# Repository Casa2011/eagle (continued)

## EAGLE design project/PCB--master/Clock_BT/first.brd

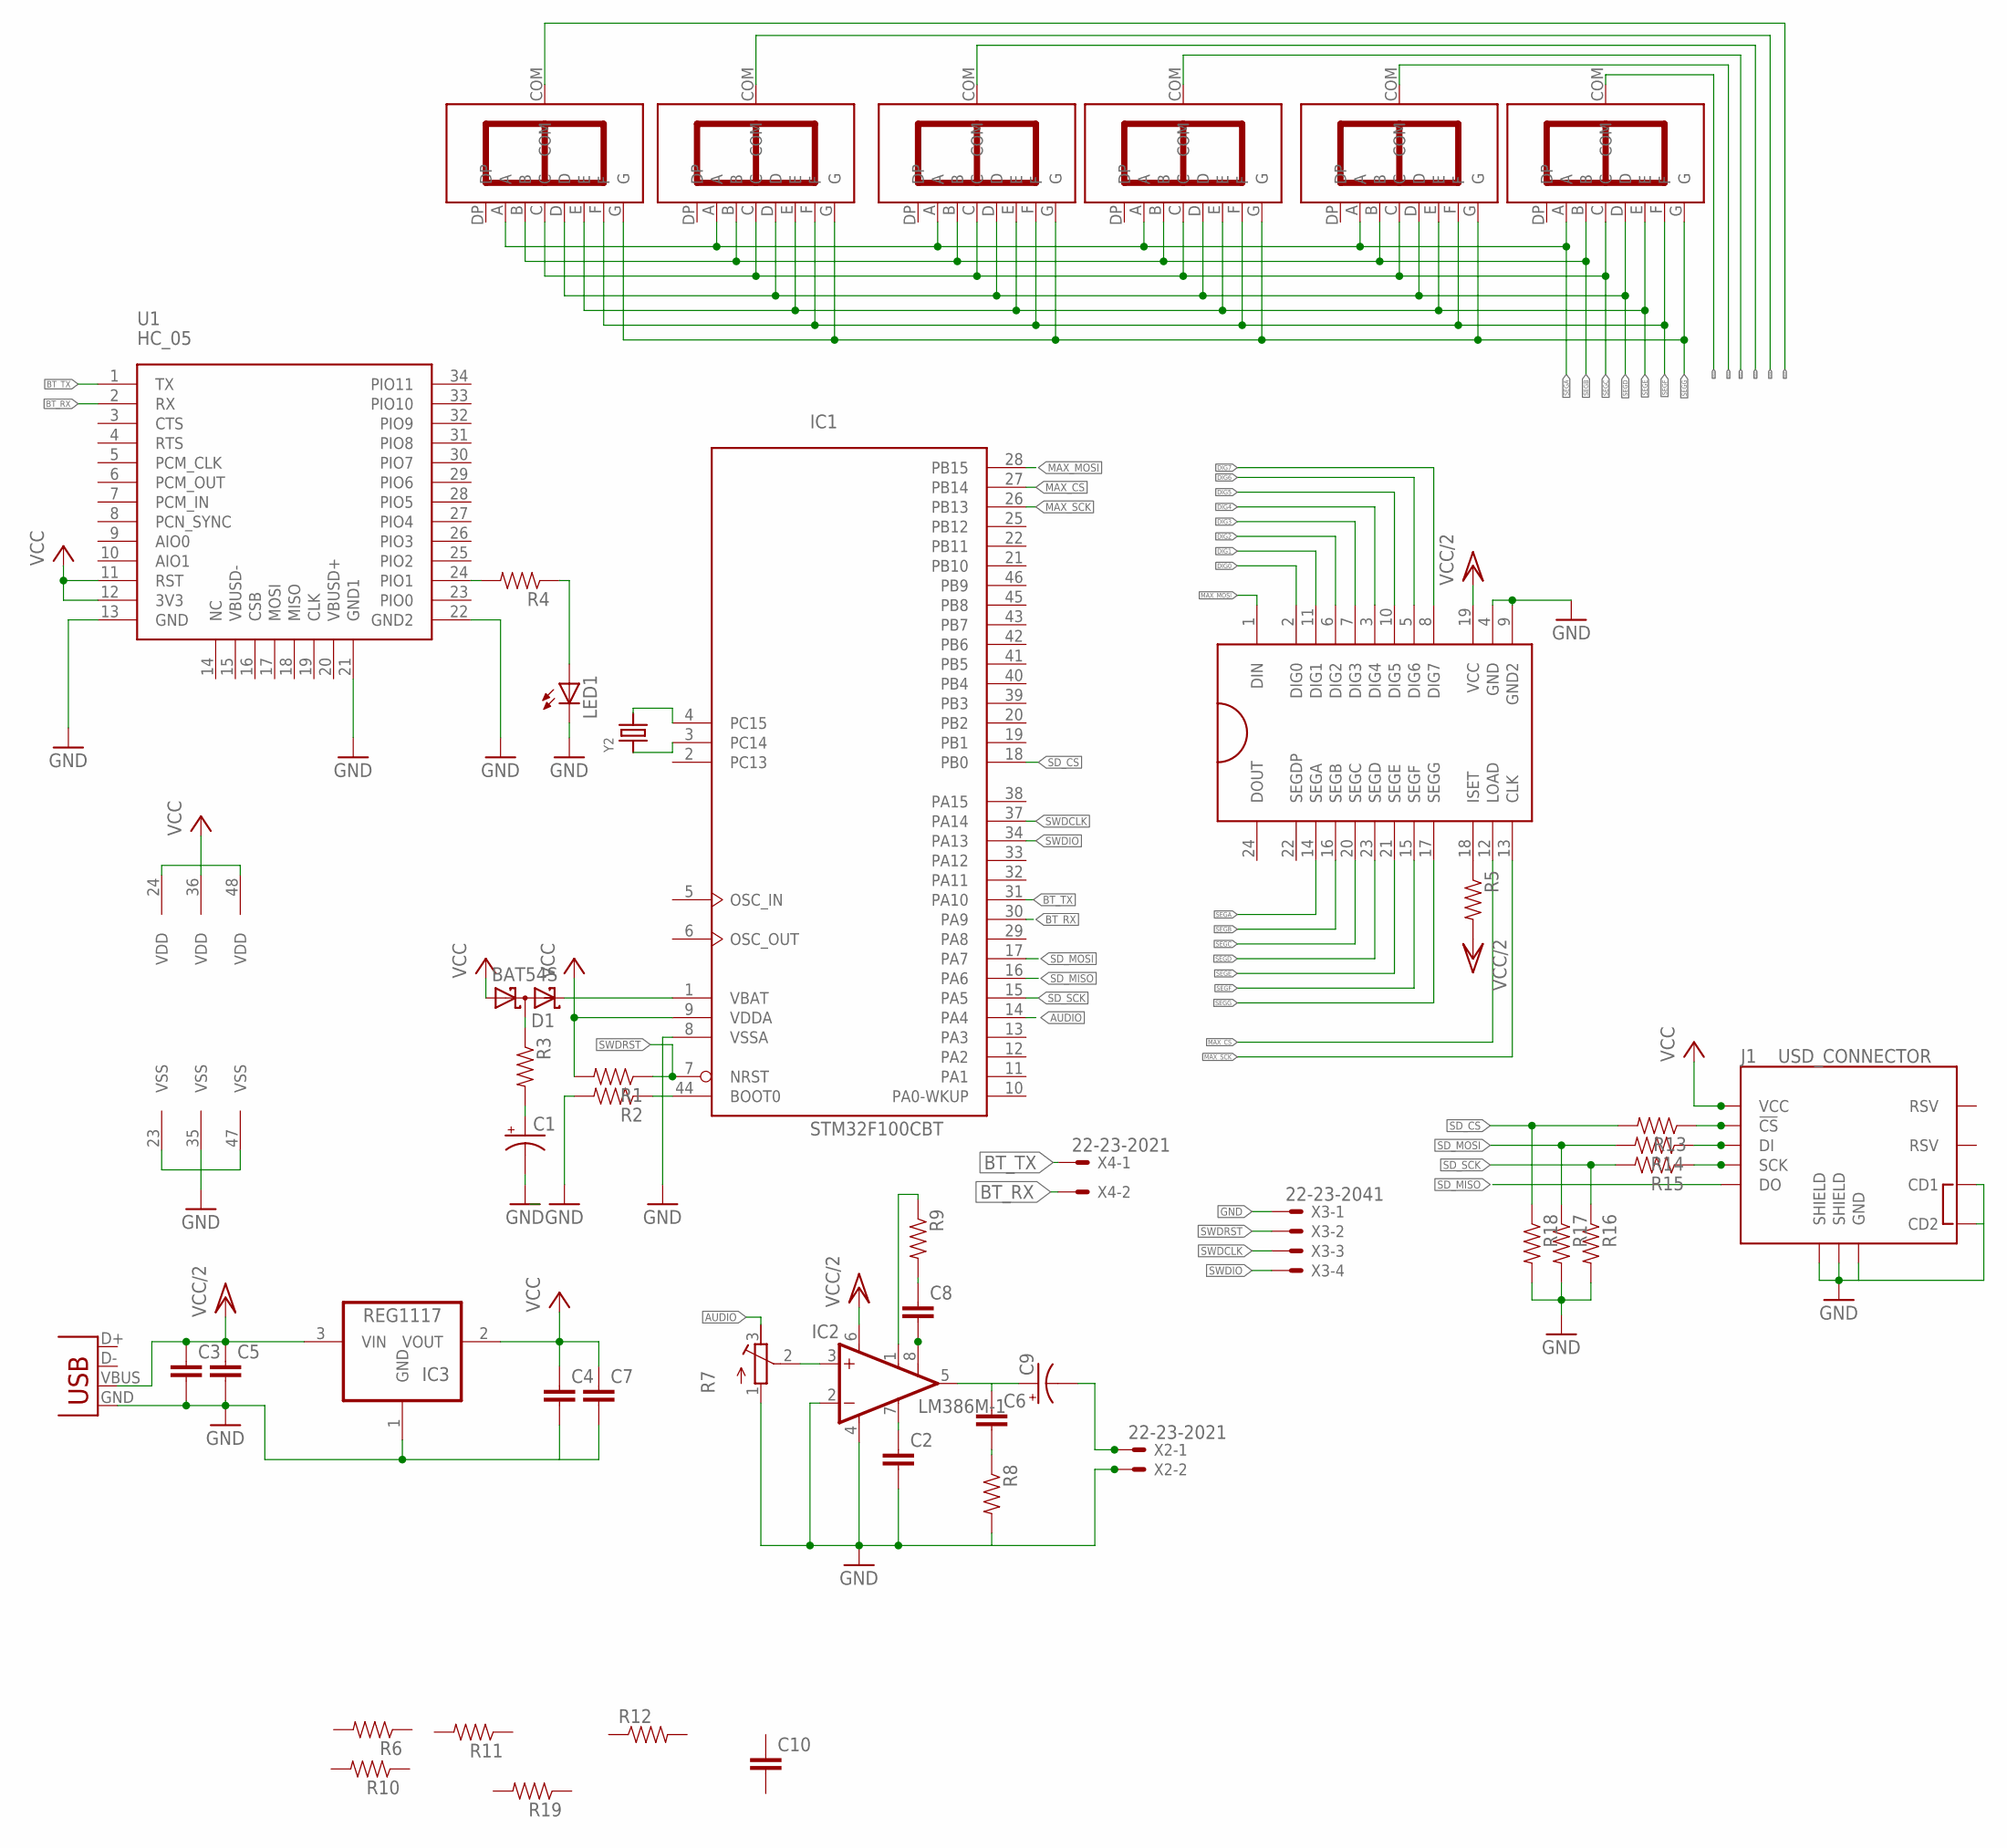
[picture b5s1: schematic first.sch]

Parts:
C1: CAP_POLPTH2; CPOL-RADIAL-10UF-25V
C2, C3, C4, C5, C6, C7, C8: C-EUC0805K; C0805K
C9: CAP_POLD; PANASONIC_D
C10: CAP0402-CAP; 0402-CAP
D1: BAT54S; SOT23
IC1: STM32F100CBT; LQFP48
IC2: LM386M-1; SO08
IC3: REG1117; SOT223
J1: USD_CONNECTOR; MICRO-SD-SOCKET-PP
LED1: LEDCHIP-LED0805; CHIP-LED0805
R1, R2, R3, R4, R5, R6, R8, R9, R10, R11, R13, R14, R15, R16, R17, R18, R19: RESISTOR0805-RES; 0805
R7: R-TRIMM4G/J; RTRIM4G/J
R12: RESISTOR0402; 0402-RES
U1: HC_05; BLUETOOTH_SMD
U$2, U$3, U$4, U$5, U$6, U$7: IV-9
U$8: MAX7219SOIK42; SO24L
X1: USBSMD; USB-MINIB
X2, X4: 22-23-2021
X3: 22-23-2041
Y2: CRYSTAL8X3.8SMT; CRYSTAL_8X3.8

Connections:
AUDIO: IC1.14 (PA4), R7.3 (E)
BT_RX: IC1.30 (PA9), U1.2 (RX), X4.2
BT_TX: IC1.31 (PA10), U1.1 (TX), X4.1
DIG0: U$7.COM, U$8.2 (DIG0)
DIG1: U$6.COM, U$8.11 (DIG1)
DIG2: U$5.COM, U$8.6 (DIG2)
DIG3: U$4.COM, U$8.7 (DIG3)
DIG4: U$3.COM, U$8.3 (DIG4)
DIG5: U$2.COM, U$8.10 (DIG5)
DIG6: U$8.5 (DIG6)
DIG7: U$8.8 (DIG7)
GND: C1.2 (-), C2.2, C3.2, C4.2, C5.2, C7.2, IC1.8 (VSSA), IC1.23 (VSS), IC1.35 (VSS), IC1.47 (VSS), IC2.2 (-IN), IC2.4 (GND), IC3.1 (GND), J1.CD1, J1.CD2, J1.GND, J1.GND1 (SHIELD), J1.GND3 (SHIELD), LED1.C, R2.2, R7.1 (A), R8.2, R16.2, R17.2, R18.2, U1.13 (GND), U1.21 (GND1), U1.22 (GND2), U$8.4 (GND), U$8.9 (GND2), X1.GND, X2.2, X3.1
MAX_CS: IC1.27 (PB14), U$8.12 (LOAD)
MAX_MOSI: IC1.28 (PB15), U$8.1 (DIN)
MAX_SCK: IC1.26 (PB13), U$8.13 (CLK)
unnamed: IC1.4 (PC15), Y2.P$4 (2)
unnamed: IC1.3 (PC14), Y2.P$1 (1)
unnamed: C1.1 (+), R3.2
unnamed: D1.2 (C2), IC1.1 (VBAT)
unnamed: R5.1, U$8.18 (ISET)
unnamed: C6.2, R8.1
unnamed: IC1.44 (BOOT0), R2.1
unnamed: C2.1, IC2.7 (BYPASS)
unnamed: IC2.3 (+IN), R7.2 (S)
unnamed: C6.1, C9.+, IC2.5 (OUT)
unnamed: C8.2, IC2.8 (GAIN)
unnamed: C8.1, R9.2
unnamed: IC2.1 (GAIN), R9.1
unnamed: C9.-, X2.1
unnamed: D1.3 (C1A2), R3.1
unnamed: R4.2, U1.24 (PIO1)
unnamed: LED1.A, R4.1
unnamed: J1.CS (!CS), R13.1
unnamed: J1.DI, R14.1
unnamed: J1.SCLK (SCK), R15.1
SD_CS: IC1.18 (PB0), R13.2, R18.1
SD_MISO: IC1.16 (PA6), J1.DO
SD_MOSI: IC1.17 (PA7), R14.2, R17.1
SD_SCK: IC1.15 (PA5), R15.2, R16.1
SEGA: U$2.A, U$3.A, U$4.A, U$5.A, U$6.A, U$7.A, U$8.14 (SEGA)
SEGB: U$2.B, U$3.B, U$4.B, U$5.B, U$6.B, U$7.B, U$8.16 (SEGB)
SEGC: U$2.C, U$3.C, U$4.C, U$5.C, U$6.C, U$7.C, U$8.20 (SEGC)
SEGD: U$2.D, U$3.D, U$4.D, U$5.D, U$6.D, U$7.D, U$8.23 (SEGD)
SEGE: U$2.E, U$3.E, U$4.E, U$5.E, U$6.E, U$7.E, U$8.21 (SEGE)
SEGF: U$2.F, U$3.F, U$4.F, U$5.F, U$6.F, U$7.F, U$8.15 (SEGF)
SEGG: U$2.G, U$3.G, U$4.G, U$5.G, U$6.G, U$7.G, U$8.17 (SEGG)
SWDCLK: IC1.37 (PA14), X3.3
SWDIO: IC1.34 (PA13), X3.4
SWDRST: IC1.7 (NRST), R1.1, X3.2
VCC: C4.1, C7.1, D1.1 (A1), IC1.9 (VDDA), IC1.24 (VDD), IC1.36 (VDD), IC1.48 (VDD), IC3.2 (VOUT), J1.VCC, R1.2, U1.11 (RST), U1.12 (3V3)
VCC/2: C3.1, C5.1, IC2.6 (VS), IC3.3 (VIN), R5.2, U$8.19 (VCC), X1.VBUS

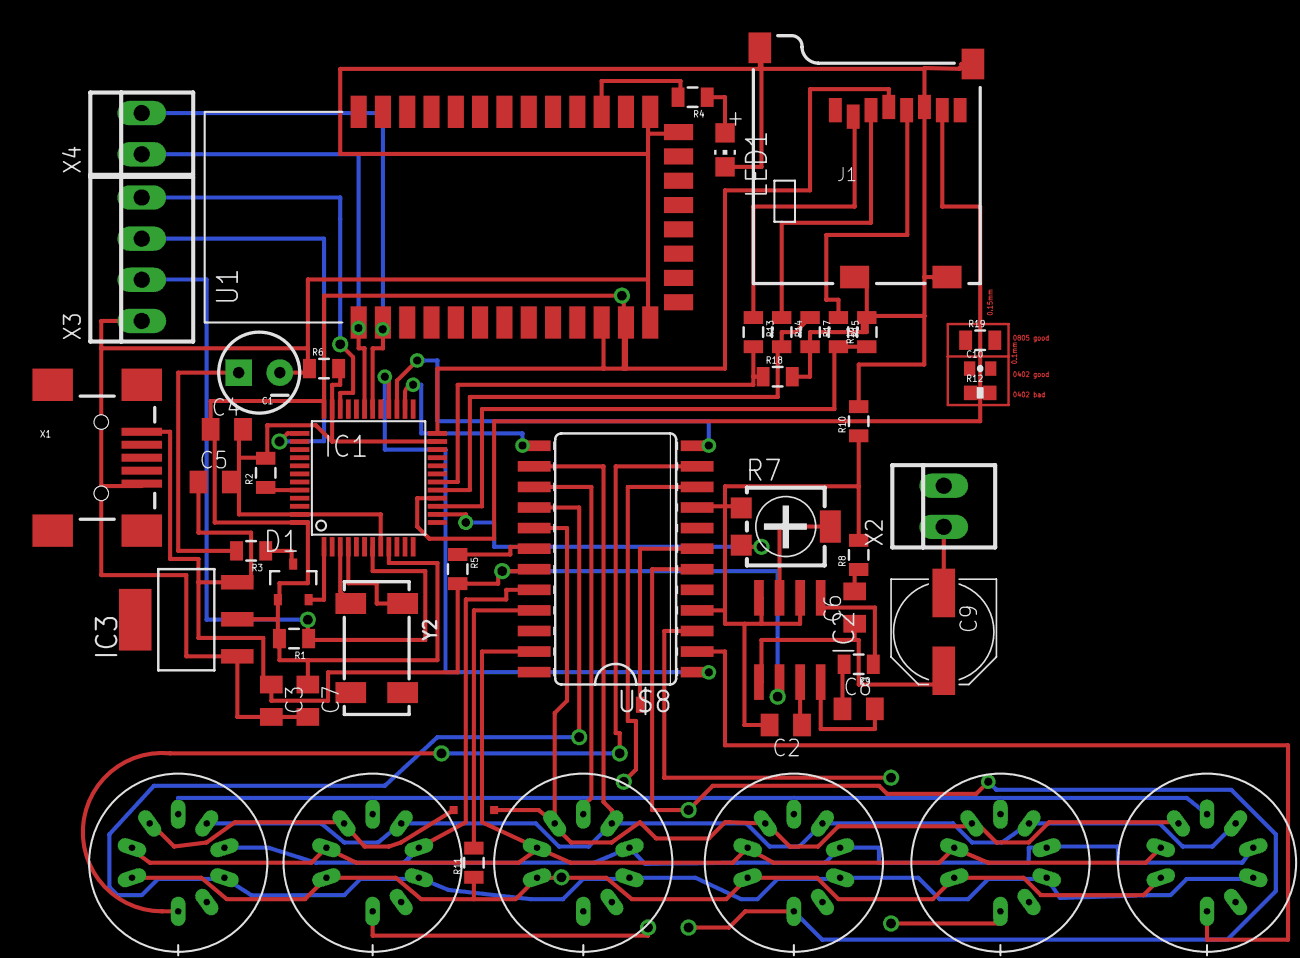
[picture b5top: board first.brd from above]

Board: 2 copper layers, 48 parts (0 on the bottom side), 49 nets.

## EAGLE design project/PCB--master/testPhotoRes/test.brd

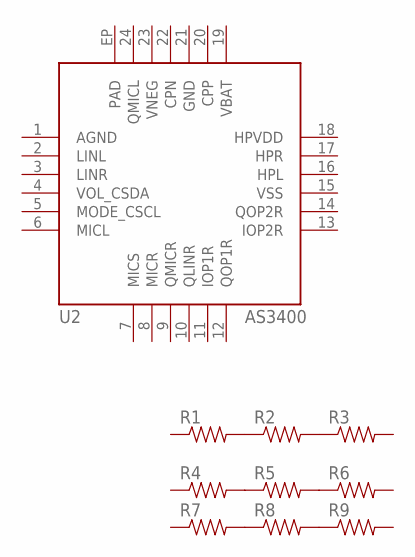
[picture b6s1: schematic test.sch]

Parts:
R1, R2, R3: RESISTOR0805-RES; 0805
R4, R5, R6: RESISTOR0603-RES; 0603-RES
R7, R8, R9: RESISTOR0402-RES; 0402-RES
U2: AS3400; QFN-24_ALT2

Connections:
unnamed: R1.2, R2.1
unnamed: R2.2, R3.1
unnamed: R4.2, R5.1
unnamed: R5.2, R6.1
unnamed: R7.2, R8.1
unnamed: R8.2, R9.1

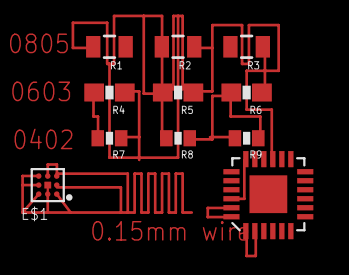
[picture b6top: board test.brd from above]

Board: 2 copper layers, 11 parts (0 on the bottom side), 6 nets.

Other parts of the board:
E$1: BGA8DS

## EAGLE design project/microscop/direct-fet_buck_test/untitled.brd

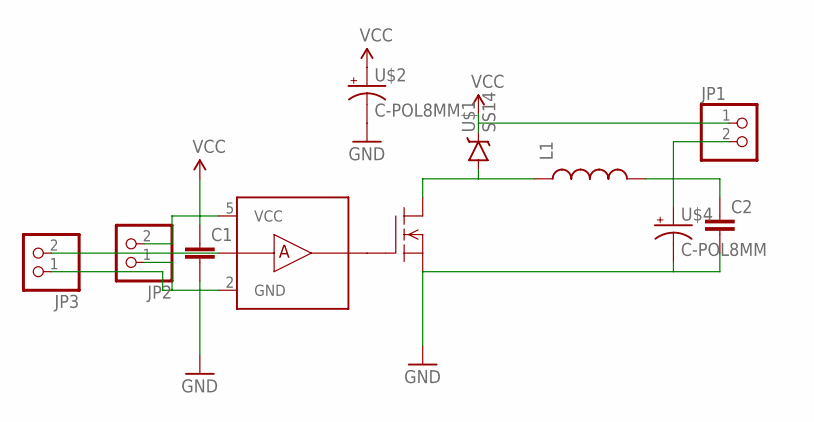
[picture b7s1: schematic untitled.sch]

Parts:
C1, C2: CC0805; C0805
JP1, JP2, JP3: PINHD-1X02_2.54; 1X02
L1: INDUCTORDR1030; DR1030
U$1: SS14; SMA-DIODE
U$2, U$4: C-POL8MM; PCAP8
U$3: DFET; DIRECT-FET
U$5: IRS44273; SOT23-5L

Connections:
GND: C1.2, C2.2, JP2.1, JP3.1, U$2.P$2 (-), U$3.S, U$3.S1 (S), U$4.P$2 (-), U$5.2 (GND)
unnamed: JP3.2, U$5.1 (INA)
unnamed: L1.1, U$1.A, U$3.D, U$3.D1 (D)
unnamed: U$3.GATE (G), U$5.3 (OUTA), U$5.4 (OUTA)
unnamed: C2.1, JP1.2, L1.2, U$4.P$1 (+)
VCC: C1.1, JP1.1, JP2.2, U$1.C, U$2.P$1 (+), U$5.5 (VCC)

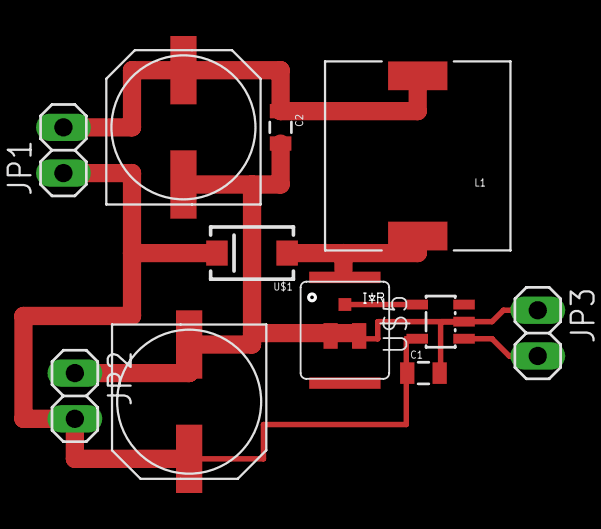
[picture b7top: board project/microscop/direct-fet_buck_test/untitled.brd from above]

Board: 5 copper layers, 11 parts (0 on the bottom side), 6 nets.

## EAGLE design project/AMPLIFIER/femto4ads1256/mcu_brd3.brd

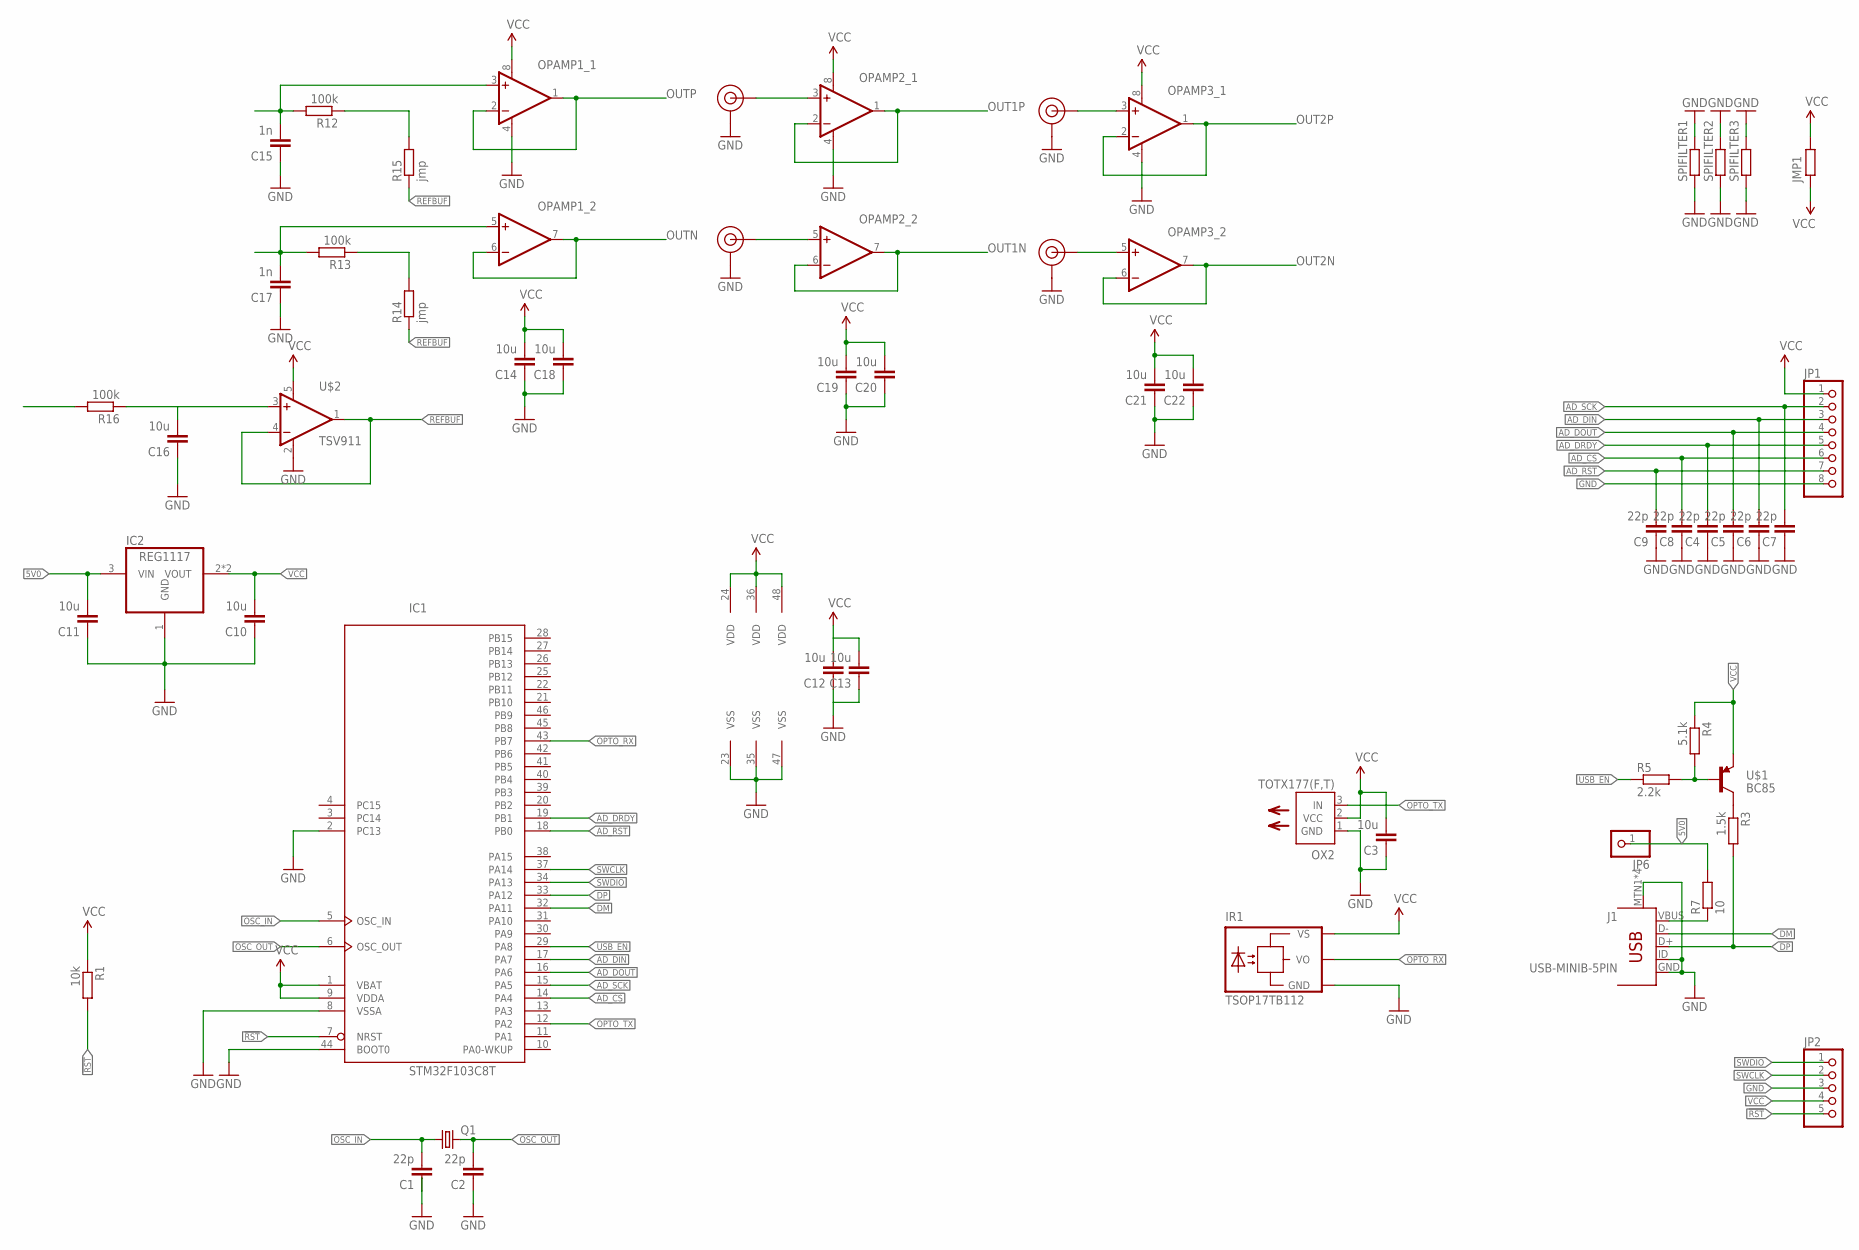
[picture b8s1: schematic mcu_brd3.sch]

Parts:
C1, C2, C4, C5, C6, C7, C8, C9: 22p; C0603
C3: 10u; C0603
C10, C11, C12, C13, C14, C16, C18, C19, C20, C21, C22: 10u; C0805
C15, C17: 1n; C0603
IC1: STM32F103C8T; LQFP48
IC2: REG1117; SOT223
IR1: TSOP17TB112; 1X03
J1: USB-MINIB-5PIN; USB-MINIB
J$1, J$2, J$3, J$4: SMA_EDGE; SMA-EDGE
JMP1: R0603; 0603
JP1: PINHD-1X8; 1X08
JP2: PINHD-1X5; 1X05
JP6: PINHD-1X1; 1X01
OPAMP1, OPAMP2, OPAMP3: LMC662; SO08
OX2: TOTX177(F,T); TOTX
Q1: CRYSTALHC49UP; HC49UP
R1: 10k; 0603
R3: 1.5k; 0603
R4: 5.1k; 0603
R5: 2.2k; 0603
R7: 10; R0805
R12, R13, R16: 100k; 0603
R14, R15: jmp; 0603
SPIFILTER1, SPIFILTER2, SPIFILTER3: R0603; 0603
U$1: BC85; SOT23
U$2: TSV911; SOT23-5L

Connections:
5V0: C11.2, IC2.3 (VIN), JP6.1, R7.2
!RST: IC1.7 (NRST), JP2.5, R1.2
AD_CS: C8.2, IC1.14 (PA4), JP1.6
AD_DIN: C6.2, IC1.17 (PA7), JP1.3
AD_DOUT: C5.2, IC1.16 (PA6), JP1.4
AD_DRDY: C4.2, IC1.19 (PB1), JP1.5
AD_RST: C9.2, IC1.18 (PB0), JP1.7
AD_SCK: C7.2, IC1.15 (PA5), JP1.2
DM: IC1.32 (PA11), J1.D-
DP: IC1.33 (PA12), J1.D+, R3.2
GND: C1.1, C2.1, C3.1, C4.1, C5.1, C6.1, C7.1, C8.1, C9.1, C10.1, C11.1, C12.1, C13.1, C14.1, C15.1, C16.1, C17.1, C18.1, C19.1, C20.1, C21.1, C22.1, IC1.2 (PC13), IC1.8 (VSSA), IC1.23 (VSS), IC1.35 (VSS), IC1.44 (BOOT0), IC1.47 (VSS), IC2.1 (GND), IR1.3 (GND), J1.GND, J1.ID, J1.MTN1, J1.MTN2 (MTN1), J1.MTN3 (MTN1), J1.MTN4 (MTN1), J$1.GND@0 (GND), J$1.GND@1 (GND), J$1.GND@2 (GND), J$1.GND@3 (GND), J$2.GND@0 (GND), J$2.GND@1 (GND), J$2.GND@2 (GND), J$2.GND@3 (GND), J$3.GND@0 (GND), J$3.GND@1 (GND), J$3.GND@2 (GND), J$3.GND@3 (GND), J$4.GND@0 (GND), J$4.GND@1 (GND), J$4.GND@2 (GND), J$4.GND@3 (GND), JP1.8, JP2.3, OPAMP1.4 (V-), OPAMP2.4 (V-), OPAMP3.4 (V-), OX2.1 (GND), SPIFILTER1.1, SPIFILTER1.2, SPIFILTER2.1, SPIFILTER2.2, SPIFILTER3.1, SPIFILTER3.2, U$2.2 (V-)
unnamed: J$2.SIG (SIGNAL), OPAMP2.5 (+IN)
unnamed: J$1.SIG (SIGNAL), OPAMP2.3 (+IN)
unnamed: R3.1, U$1.3 (C)
unnamed: R4.2, R5.2, U$1.1 (B)
unnamed: J$4.SIG (SIGNAL), OPAMP3.5 (+IN)
unnamed: C17.2, OPAMP1.5 (+IN), R13.2
unnamed: J$3.SIG (SIGNAL), OPAMP3.3 (+IN)
unnamed: R12.1, R15.2
unnamed: C15.2, OPAMP1.3 (+IN), R12.2
unnamed: R13.1, R14.2
unnamed: C16.2, R16.1, U$2.3 (+IN)
OPTO_RX: IC1.43 (PB7), IR1.1 (VO)
OPTO_TX: IC1.12 (PA2), OX2.3 (IN)
OSC_IN: C1.2, IC1.5 (OSC_IN), Q1.1
OSC_OUT: C2.2, IC1.6 (OSC_OUT), Q1.2
OUT1N: OPAMP2.6 (-IN), OPAMP2.7 (OUT)
OUT1P: OPAMP2.1 (OUT), OPAMP2.2 (-IN)
OUT2N: OPAMP3.6 (-IN), OPAMP3.7 (OUT)
OUT2P: OPAMP3.1 (OUT), OPAMP3.2 (-IN)
OUTN: OPAMP1.6 (-IN), OPAMP1.7 (OUT)
OUTP: OPAMP1.1 (OUT), OPAMP1.2 (-IN)
REFBUF: R14.1, R15.1, U$2.1 (OUT), U$2.4 (-IN)
SWCLK: IC1.37 (PA14), JP2.2
SWDIO: IC1.34 (PA13), JP2.1
USB_EN: IC1.29 (PA8), R5.1
VBUS: J1.VBUS, R7.1
VCC: C3.2, C10.2, C12.2, C13.2, C14.2, C18.2, C19.2, C20.2, C21.2, C22.2, IC1.1 (VBAT), IC1.9 (VDDA), IC1.24 (VDD), IC1.36 (VDD), IC1.48 (VDD), IC2.2 (VOUT), IC2.4 (VOUT), IR1.2 (VS), JMP1.1, JMP1.2, JP1.1, JP2.4, OPAMP1.8 (V+), OPAMP2.8 (V+), OPAMP3.8 (V+), OX2.2 (VCC), R1.1, R4.1, U$1.2 (E), U$2.5 (V+)

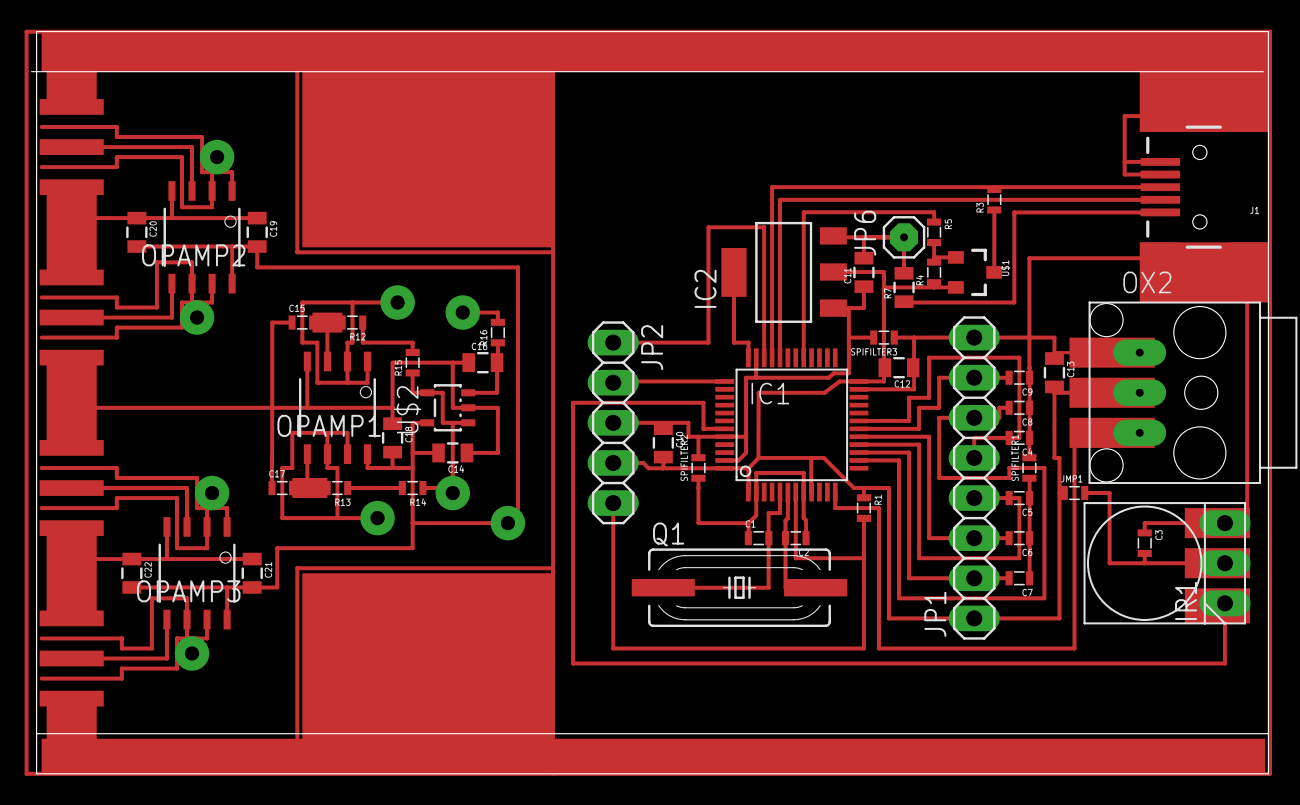
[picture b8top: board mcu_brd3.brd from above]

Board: 2 copper layers, 78.0 x 47.0 mm, 54 parts (0 on the bottom side), 38 nets.

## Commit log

2018-07-21 add lib
2018-07-21 test project
2018-07-21 add ulp
2018-07-21 default grid setting
2018-07-23 old project and custom menu
2018-07-25 fix lbr(add)
2018-07-25 fix lbr(add1)
2018-07-25 fix lbr(add2)
2018-07-25 fix lbr(add4)
2018-07-25 bintoxml lbr(add)
2018-07-25 my lib add
